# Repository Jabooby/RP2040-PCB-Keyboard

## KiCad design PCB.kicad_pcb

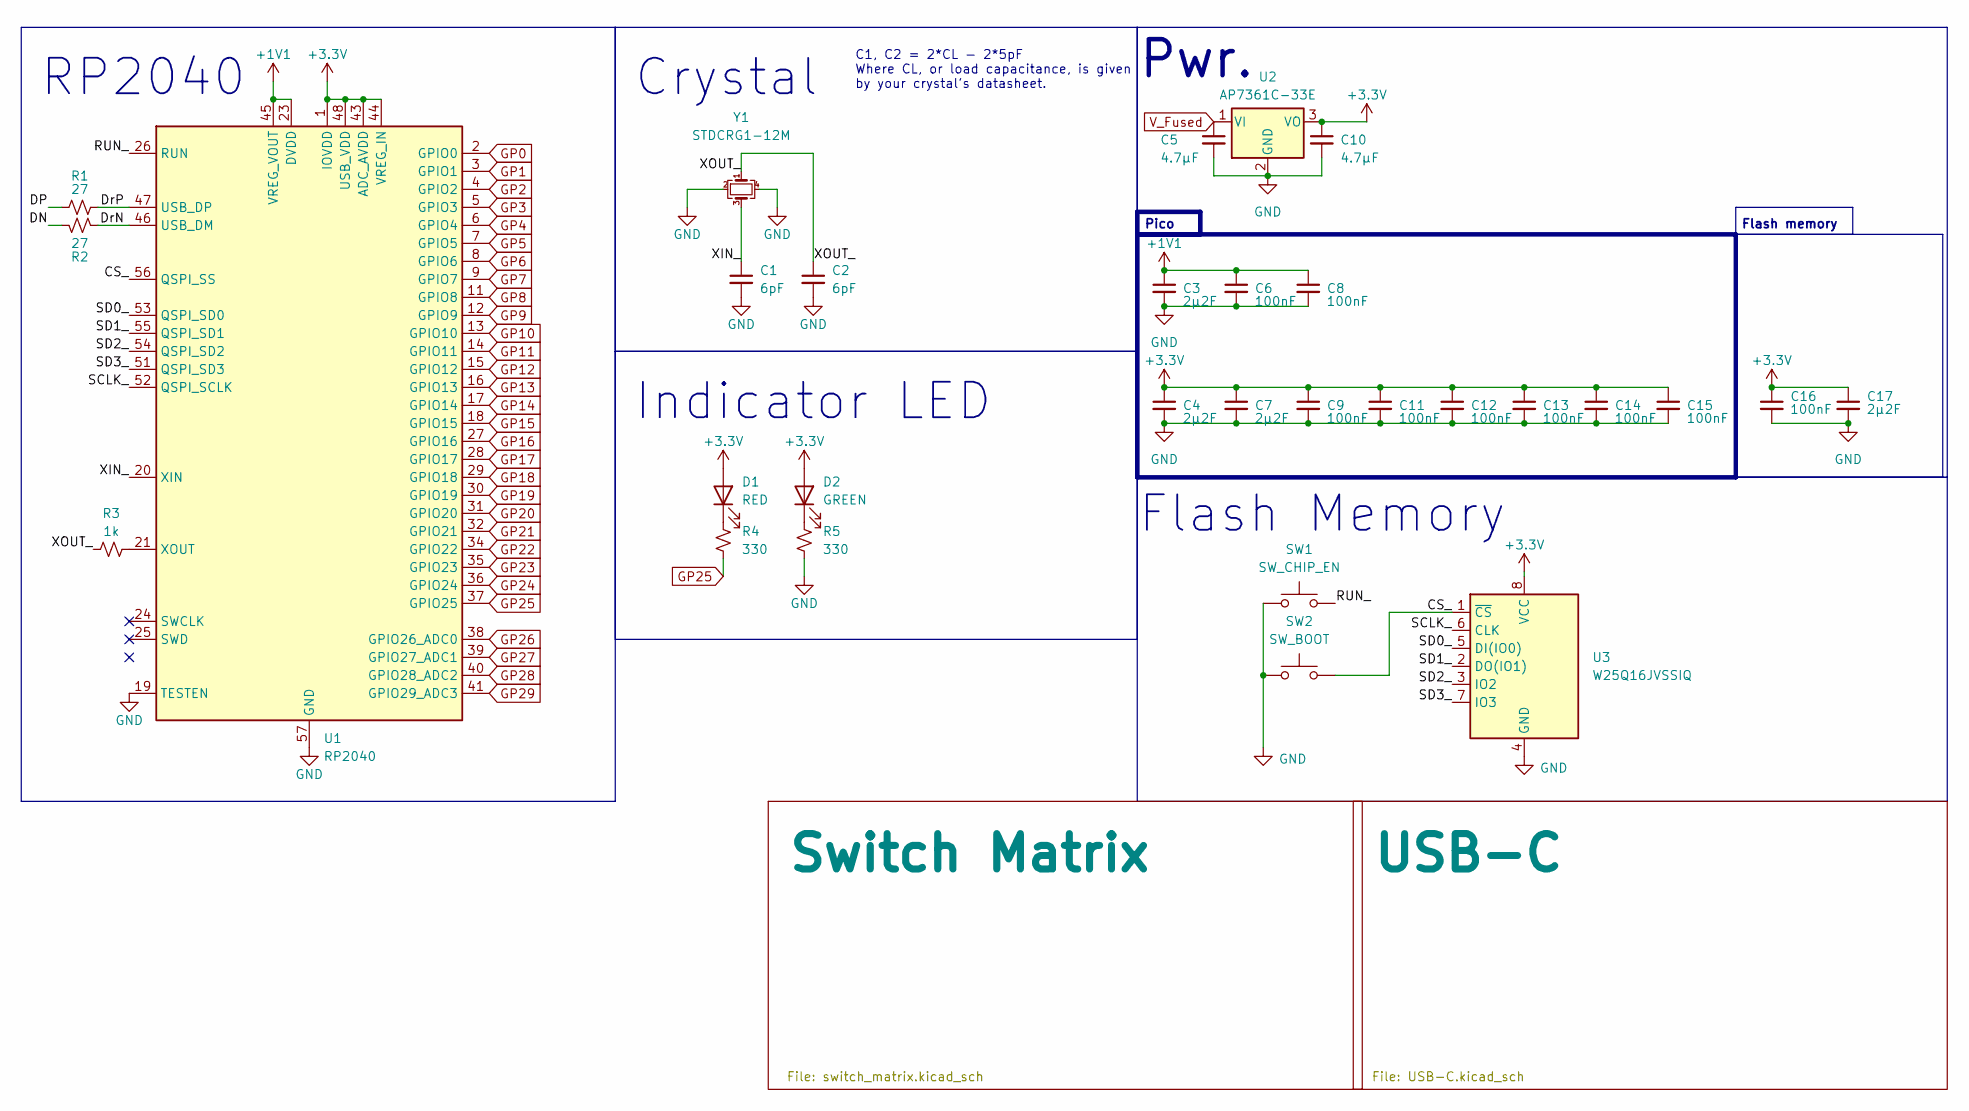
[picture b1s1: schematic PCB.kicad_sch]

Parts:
C1, C2: 6pF; C_0402_1005Metric; LCSC C1562
C3, C4, C17: 2µ2F; C_0805_2012Metric; LCSC C52923
C5, C10: 4.7µF; C_0805_2012Metric; LCSC C52923
C6, C8, C9, C11, C12, C13, C14, C15: 100nF; C_0402_1005Metric; LCSC C1525
C7: 2µ2F; C_0805_2012Metric; LCSC C1525
C16: 100nF; C_0402_1005Metric; LCSC C52923
D1: RED; D_0805_2012Metric
D2: GREEN; D_0805_2012Metric
R1, R2: 27; R_0603_1608Metric; LCSC C25152
R3: 1k; R_0603_1608Metric; LCSC C106235
R4, R5: 330; R_0603_1608Metric
SW1: SW_CHIP_EN; SW_DIP_SPSTx01_Slide_6.7x4.1mm_W6.73mm_P2.54mm_LowProfile_J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
SW2: SW_BOOT; SW_DIP_SPSTx01_Slide_6.7x4.1mm_W6.73mm_P2.54mm_LowProfile_J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
U1: RP2040; QFN-56-1EP_7x7mm_P0.4mm_EP3.2x3.2mm_ThermalVias; LCSC C2040
U2: AP7361C-33E; SOT-223-3_TabPin2
U3: W25Q16JVSSIQ; SOIC-8_5.23x5.23mm_P1.27mm
Y1: STDCRG1-12M; Crystal_SMD_3225-4Pin_3.2x2.5mm; LCSC C9002

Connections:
+1V1: C3.1, C6.1, C8.1, U1.23 (DVDD), U1.45 (VREG_VOUT), U1.50 (DVDD)
+3.3V: C4.1, C7.1, C9.1, C10.1, C11.1, C12.1, C13.1, C14.1, C15.1, C16.1, C17.1, D1.2 (A), D2.2 (A), U1.1 (IOVDD), U1.10 (IOVDD), U1.22 (IOVDD), U1.33 (IOVDD), U1.42 (IOVDD), U1.43 (ADC_AVDD), U1.44 (VREG_IN), U1.48 (USB_VDD), U1.49 (IOVDD), U2.3 (VO), U3.8 (VCC)
/CS_: SW2.2, U1.56 (QSPI_SS), U3.1 (~CS)
/DN: R2.2
/DP: R1.1
/DrN: R2.1, U1.46 (USB_DM)
/DrP: R1.2, U1.47 (USB_DP)
/RUN_: SW1.2, U1.26 (RUN)
/SCLK_: U1.52 (QSPI_SCLK), U3.6 (CLK)
/SD0_: U1.53 (QSPI_SD0), U3.5 (DI(IO0))
/SD1_: U1.55 (QSPI_SD1), U3.2 (DO(IO1))
/SD2_: U1.54 (QSPI_SD2), U3.3 (IO2)
/SD3_: U1.51 (QSPI_SD3), U3.7 (IO3)
/XIN_: C1.1, U1.20 (XIN), Y1.3
/XOUT_: C2.1, R3.1, Y1.1
GND: C1.2, C2.2, C3.2, C4.2, C5.2, C6.2, C7.2, C8.2, C9.2, C10.2, C11.2, C12.2, C13.2, C14.2, C15.2, C16.2, C17.2, R5.2, SW1.1, SW2.1, U1.19 (TESTEN), U1.57 (GND), U2.2 (GND), U3.4 (GND), Y1.2, Y1.4; also elsewhere on the board
GP0: U1.2 (GPIO0); also elsewhere on the board
GP1: U1.3 (GPIO1); also elsewhere on the board
GP2: U1.4 (GPIO2); also elsewhere on the board
GP3: U1.5 (GPIO3); also elsewhere on the board
GP4: U1.6 (GPIO4); also elsewhere on the board
GP5: U1.7 (GPIO5); also elsewhere on the board
GP6: U1.8 (GPIO6); also elsewhere on the board
GP7: U1.9 (GPIO7); also elsewhere on the board
GP8: U1.11 (GPIO8); also elsewhere on the board
GP9: U1.12 (GPIO9); also elsewhere on the board
GP10: U1.13 (GPIO10); also elsewhere on the board
GP11: U1.14 (GPIO11); also elsewhere on the board
GP12: U1.15 (GPIO12); also elsewhere on the board
GP13: U1.16 (GPIO13); also elsewhere on the board
GP14: U1.17 (GPIO14); also elsewhere on the board
GP15: U1.18 (GPIO15); also elsewhere on the board
GP16: U1.27 (GPIO16); also elsewhere on the board
GP17: U1.28 (GPIO17); also elsewhere on the board
GP18: U1.29 (GPIO18); also elsewhere on the board
GP19: U1.30 (GPIO19)
GP20: U1.31 (GPIO20)
GP21: U1.32 (GPIO21)
GP22: U1.34 (GPIO22)
GP23: U1.35 (GPIO23)
GP24: U1.36 (GPIO24)
GP25: R4.2, U1.37 (GPIO25)
GP26: U1.38 (GPIO26_ADC0)
GP27: U1.39 (GPIO27_ADC1)
GP28: U1.40 (GPIO28_ADC2)
GP29: U1.41 (GPIO29_ADC3)
unnamed: D1.1 (K), R4.1
unnamed: D2.1 (K), R5.1
unnamed: R3.2, U1.21 (XOUT)
V_Fused: C5.1, U2.1 (VI); also elsewhere on the board

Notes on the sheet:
Flash memory
Flash Memory
Pwr.
C1, C2 = 2*CL - 2*5pF Where CL, or load capacitance, is given by your crystal's datasheet.
Pico
Indicator LED
Crystal
RP2040

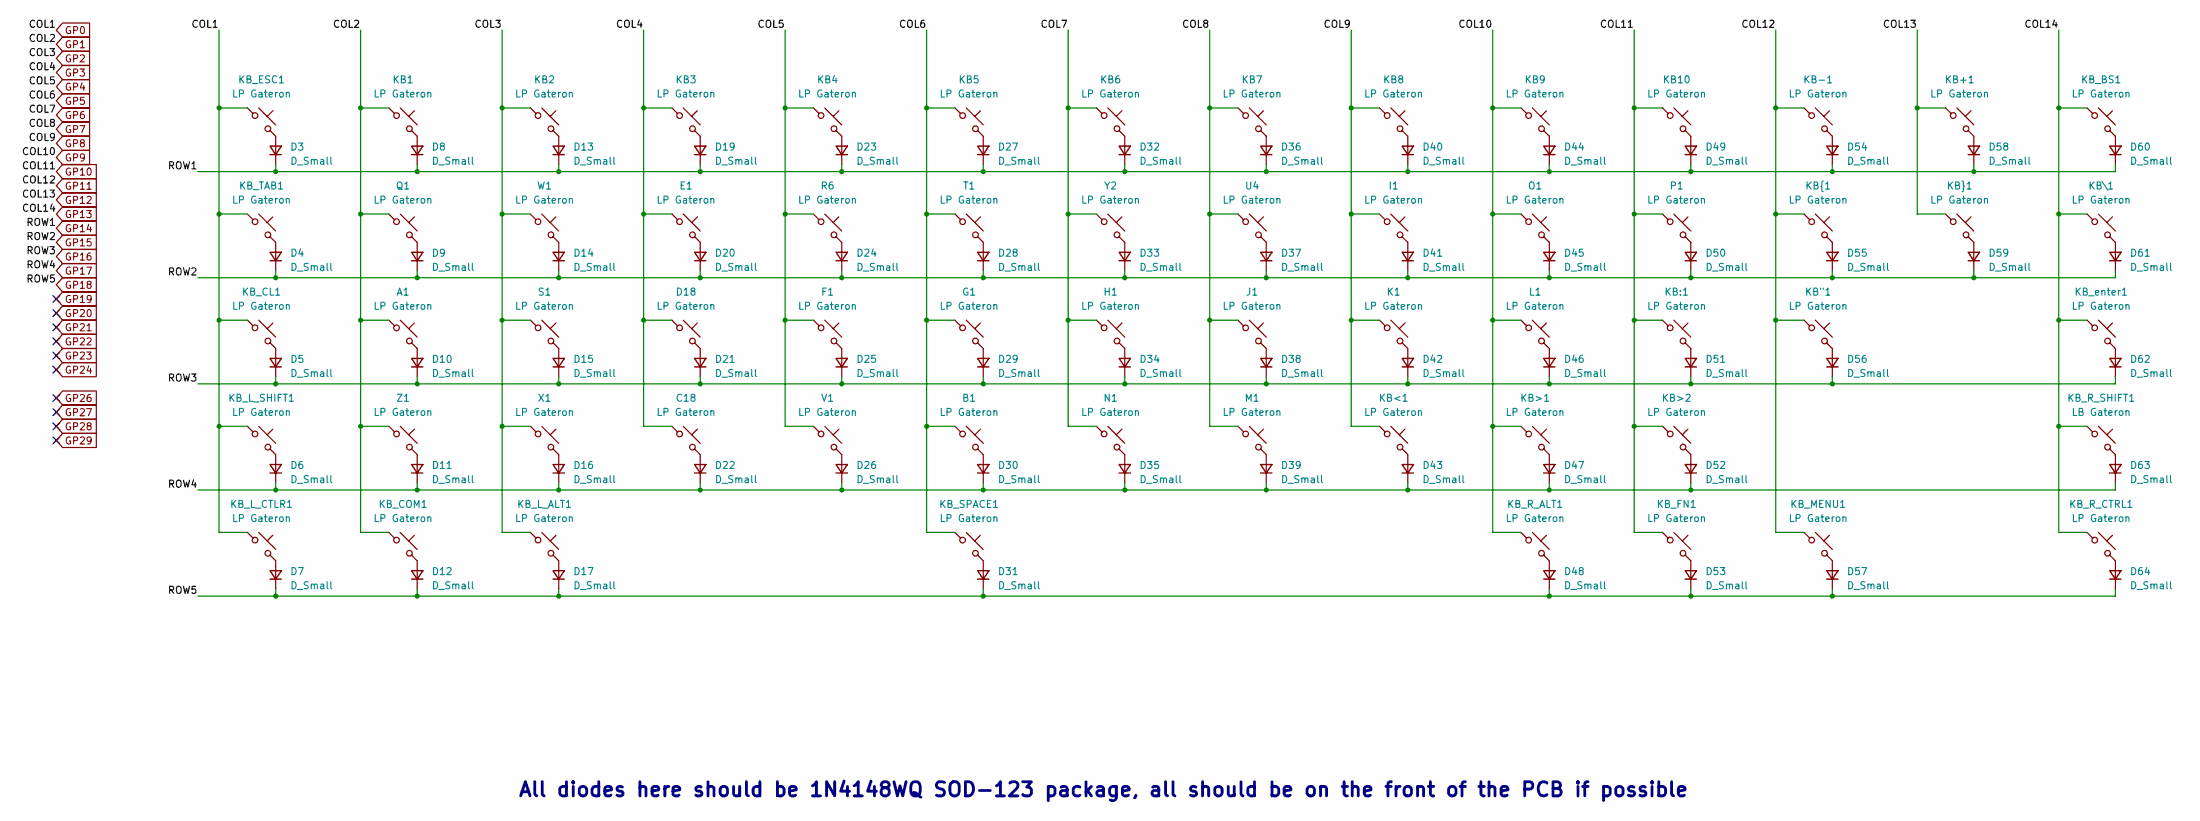
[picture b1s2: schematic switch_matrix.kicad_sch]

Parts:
A1: LP Gateron; SW_Gateron_LowProfile_THT
B1: LP Gateron; SW_Gateron_LowProfile_THT
C18: LP Gateron; SW_Gateron_LowProfile_THT
D3, D4, D5, D6, D7, D8, D9, D10, D11, D12, D13, D14, D15, D16, D17, D19, D20, D21, D22, D23, D24, D25, D26, D27, D28, D29, D30, D31, D32, D33, D34, D35, D36, D37, D38, D39, D40, D41, D42, D43, D44, D45, D46, D47, D48, D49, D50, D51, D52, D53, D54, D55, D56, D57, D58, D59, D60, D61, D62, D63, D64: D_Small; D_SOD-123; LCSC C81598
D18: LP Gateron; SW_Gateron_LowProfile_THT
E1: LP Gateron; SW_Gateron_LowProfile_THT
F1: LP Gateron; SW_Gateron_LowProfile_THT
G1: LP Gateron; SW_Gateron_LowProfile_THT
H1: LP Gateron; SW_Gateron_LowProfile_THT
I1: LP Gateron; SW_Gateron_LowProfile_THT
J1: LP Gateron; SW_Gateron_LowProfile_THT
K1: LP Gateron; SW_Gateron_LowProfile_THT
KB1, KB2, KB3, KB4, KB5, KB6, KB7, KB8, KB9, KB10: LP Gateron; SW_Gateron_LowProfile_THT
KB"1: LP Gateron; SW_Gateron_LowProfile_THT
KB+1: LP Gateron; SW_Gateron_LowProfile_THT
KB-1: LP Gateron; SW_Gateron_LowProfile_THT
KB:1: LP Gateron; SW_Gateron_LowProfile_THT
KB<1: LP Gateron; SW_Gateron_LowProfile_THT
KB>1, KB>2: LP Gateron; SW_Gateron_LowProfile_THT
KB\1: LP Gateron; SW_Gateron_LowProfile_THT
KB_BS1: LP Gateron; SW_Gateron_LowProfile_THT
KB_CL1: LP Gateron; SW_Gateron_LowProfile_THT
KB_COM1: LP Gateron; SW_Gateron_LowProfile_THT
KB_ESC1: LP Gateron; SW_Gateron_LowProfile_THT
KB_FN1: LP Gateron; SW_Gateron_LowProfile_THT
KB_L_ALT1: LP Gateron; SW_Gateron_LowProfile_THT
KB_L_CTLR1: LP Gateron; SW_Gateron_LowProfile_THT
KB_L_SHIFT1: LP Gateron; SW_Gateron_LowProfile_THT
KB_MENU1: LP Gateron; SW_Gateron_LowProfile_THT
KB_R_ALT1: LP Gateron; SW_Gateron_LowProfile_THT
KB_R_CTRL1: LP Gateron; SW_Gateron_LowProfile_THT
KB_R_SHIFT1: LB Gateron; SW_Gateron_LowProfile_THT
KB_SPACE1: LP Gateron; SW_Gateron_LowProfile_THT
KB_TAB1: LP Gateron; SW_Gateron_LowProfile_THT
KB_enter1: LP Gateron; SW_Gateron_LowProfile_THT
KB{1: LP Gateron; SW_Gateron_LowProfile_THT
KB}1: LP Gateron; SW_Gateron_LowProfile_THT
L1: LP Gateron; SW_Gateron_LowProfile_THT
M1: LP Gateron; SW_Gateron_LowProfile_THT
N1: LP Gateron; SW_Gateron_LowProfile_THT
O1: LP Gateron; SW_Gateron_LowProfile_THT
P1: LP Gateron; SW_Gateron_LowProfile_THT
Q1: LP Gateron; SW_Gateron_LowProfile_THT
R6: LP Gateron; SW_Gateron_LowProfile_THT
S1: LP Gateron; SW_Gateron_LowProfile_THT
T1: LP Gateron; SW_Gateron_LowProfile_THT
U4: LP Gateron; SW_Gateron_LowProfile_THT
V1: LP Gateron; SW_Gateron_LowProfile_THT
W1: LP Gateron; SW_Gateron_LowProfile_THT
X1: LP Gateron; SW_Gateron_LowProfile_THT
Y2: LP Gateron; SW_Gateron_LowProfile_THT
Z1: LP Gateron; SW_Gateron_LowProfile_THT

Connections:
GP0: KB_CL1.1, KB_ESC1.1, KB_L_CTLR1.1, KB_L_SHIFT1.1, KB_TAB1.1; also elsewhere on the board
GP1: A1.1, KB1.1, KB_COM1.1, Q1.1, Z1.1; also elsewhere on the board
GP2: KB2.1, KB_L_ALT1.1, S1.1, W1.1, X1.1; also elsewhere on the board
GP3: C18.1, D18.1, E1.1, KB3.1; also elsewhere on the board
GP4: F1.1, KB4.1, R6.1, V1.1; also elsewhere on the board
GP5: B1.1, G1.1, KB5.1, KB_SPACE1.1, T1.1; also elsewhere on the board
GP6: H1.1, KB6.1, N1.1, Y2.1; also elsewhere on the board
GP7: J1.1, KB7.1, M1.1, U4.1; also elsewhere on the board
GP8: I1.1, K1.1, KB8.1, KB<1.1; also elsewhere on the board
GP9: KB9.1, KB>1.1, KB_R_ALT1.1, L1.1, O1.1; also elsewhere on the board
GP10: KB10.1, KB:1.1, KB>2.1, KB_FN1.1, P1.1; also elsewhere on the board
GP11: KB"1.1, KB-1.1, KB_MENU1.1, KB{1.1; also elsewhere on the board
GP12: KB+1.1, KB}1.1; also elsewhere on the board
GP13: KB\1.1, KB_BS1.1, KB_R_CTRL1.1, KB_R_SHIFT1.1, KB_enter1.1; also elsewhere on the board
GP14: D3.1 (K), D8.1 (K), D13.1 (K), D19.1 (K), D23.1 (K), D27.1 (K), D32.1 (K), D36.1 (K), D40.1 (K), D44.1 (K), D49.1 (K), D54.1 (K), D58.1 (K), D60.1 (K); also elsewhere on the board
GP15: D4.1 (K), D9.1 (K), D14.1 (K), D20.1 (K), D24.1 (K), D28.1 (K), D33.1 (K), D37.1 (K), D41.1 (K), D45.1 (K), D50.1 (K), D55.1 (K), D59.1 (K), D61.1 (K); also elsewhere on the board
GP16: D5.1 (K), D10.1 (K), D15.1 (K), D21.1 (K), D25.1 (K), D29.1 (K), D34.1 (K), D38.1 (K), D42.1 (K), D46.1 (K), D51.1 (K), D56.1 (K), D62.1 (K); also elsewhere on the board
GP17: D6.1 (K), D11.1 (K), D16.1 (K), D22.1 (K), D26.1 (K), D30.1 (K), D35.1 (K), D39.1 (K), D43.1 (K), D47.1 (K), D52.1 (K), D63.1 (K); also elsewhere on the board
GP18: D7.1 (K), D12.1 (K), D17.1 (K), D31.1 (K), D48.1 (K), D53.1 (K), D57.1 (K), D64.1 (K); also elsewhere on the board
unnamed: D3.2 (A), KB_ESC1.2
unnamed: D4.2 (A), KB_TAB1.2
unnamed: D5.2 (A), KB_CL1.2
unnamed: D6.2 (A), KB_L_SHIFT1.2
unnamed: D7.2 (A), KB_L_CTLR1.2
unnamed: D8.2 (A), KB1.2
unnamed: D9.2 (A), Q1.2
unnamed: A1.2, D10.2 (A)
unnamed: D11.2 (A), Z1.2
unnamed: D12.2 (A), KB_COM1.2
unnamed: D13.2 (A), KB2.2
unnamed: D14.2 (A), W1.2
unnamed: D15.2 (A), S1.2
unnamed: D16.2 (A), X1.2
unnamed: D17.2 (A), KB_L_ALT1.2
unnamed: D19.2 (A), KB3.2
unnamed: D20.2 (A), E1.2
unnamed: D18.2, D21.2 (A)
unnamed: C18.2, D22.2 (A)
unnamed: D23.2 (A), KB4.2
unnamed: D24.2 (A), R6.2
unnamed: D25.2 (A), F1.2
unnamed: D26.2 (A), V1.2
unnamed: D27.2 (A), KB5.2
unnamed: D28.2 (A), T1.2
unnamed: D29.2 (A), G1.2
unnamed: B1.2, D30.2 (A)
unnamed: D31.2 (A), KB_SPACE1.2
unnamed: D32.2 (A), KB6.2
unnamed: D33.2 (A), Y2.2
unnamed: D34.2 (A), H1.2
unnamed: D35.2 (A), N1.2
unnamed: D36.2 (A), KB7.2
unnamed: D37.2 (A), U4.2
unnamed: D38.2 (A), J1.2
unnamed: D39.2 (A), M1.2
unnamed: D40.2 (A), KB8.2
unnamed: D41.2 (A), I1.2
unnamed: D42.2 (A), K1.2
unnamed: D43.2 (A), KB<1.2
unnamed: D44.2 (A), KB9.2
unnamed: D45.2 (A), O1.2
unnamed: D46.2 (A), L1.2
unnamed: D47.2 (A), KB>1.2
unnamed: D48.2 (A), KB_R_ALT1.2
unnamed: D49.2 (A), KB10.2
unnamed: D50.2 (A), P1.2
unnamed: D51.2 (A), KB:1.2
unnamed: D52.2 (A), KB>2.2
unnamed: D53.2 (A), KB_FN1.2
unnamed: D54.2 (A), KB-1.2
unnamed: D55.2 (A), KB{1.2
unnamed: D56.2 (A), KB"1.2
unnamed: D57.2 (A), KB_MENU1.2
unnamed: D58.2 (A), KB+1.2
unnamed: D59.2 (A), KB}1.2
unnamed: D60.2 (A), KB_BS1.2
unnamed: D61.2 (A), KB\1.2
unnamed: D62.2 (A), KB_enter1.2
unnamed: D63.2 (A), KB_R_SHIFT1.2
unnamed: D64.2 (A), KB_R_CTRL1.2

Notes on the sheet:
All diodes here should be 1N4148WQ SOD-123 package, all should be on the front of the PCB if possible

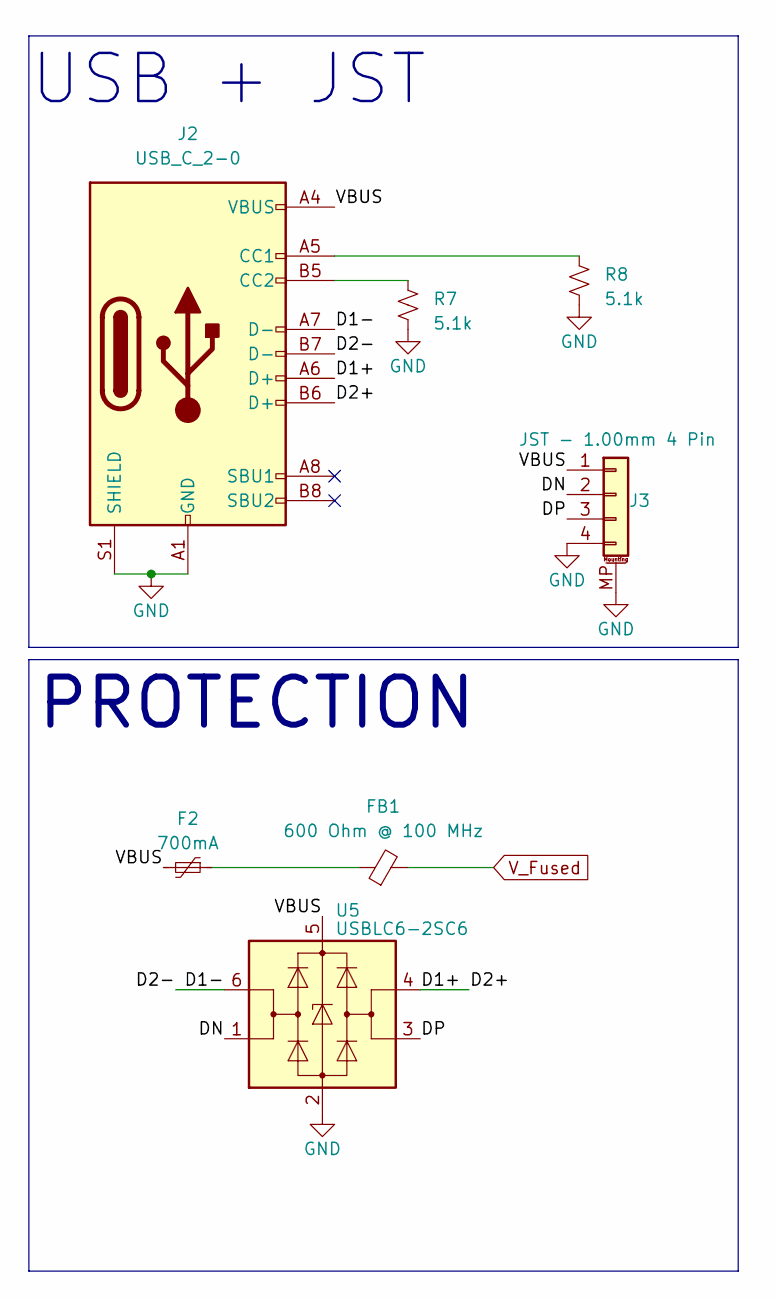
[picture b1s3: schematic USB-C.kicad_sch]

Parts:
F2: 700mA; Fuse_0805_2012Metric; LCSC C914086
FB1: 600 Ohm @ 100 MHz; L_0805_2012Metric; LCSC C85812
J2: USB_C_2-0; USB_C_Receptacle_G-Switch_GT-USB-7010ASV
J3: JST - 1.00mm 4 Pin; JST_SH_SM04B-SRSS-TB_1x04-1MP_P1.00mm_Horizontal; LCSC C160404
R7, R8: 5.1k; R_0603_1608Metric; LCSC C25905
U5: USBLC6-2SC6; SOT-23-6; LCSC C558442

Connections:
/USB-C/D1+: J2.A6 (D+), J2.B6 (D+), U5.4 (I/O2)
/USB-C/D1-: J2.A7 (D-), J2.B7 (D-), U5.6 (I/O1)
/USB-C/DN: J3.2, U5.1 (I/O1)
/USB-C/DP: J3.3, U5.3 (I/O2)
/USB-C/VBUS: F2.2, J2.A4 (VBUS), J2.A9 (VBUS), J2.B4 (VBUS), J2.B9 (VBUS), J3.1, U5.5 (VBUS)
GND: J2.A1 (GND), J2.A12 (GND), J2.B1 (GND), J2.B12 (GND), J2.S1 (SHIELD), J3.4, J3.MP (MountPin), R7.1, R8.1, U5.2 (GND); also elsewhere on the board
unnamed: F2.1, FB1.1
unnamed: J2.A5 (CC1), R8.2
unnamed: J2.B5 (CC2), R7.2
V_Fused: FB1.2; also elsewhere on the board

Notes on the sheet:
USB + JST
PROTECTION

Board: 4 copper layers, 162 parts (96 on the bottom side), 107 nets, no tracks yet.

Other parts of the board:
H3, H5: MountingHole; PKRHSL
H4: MountingHole; PKRH

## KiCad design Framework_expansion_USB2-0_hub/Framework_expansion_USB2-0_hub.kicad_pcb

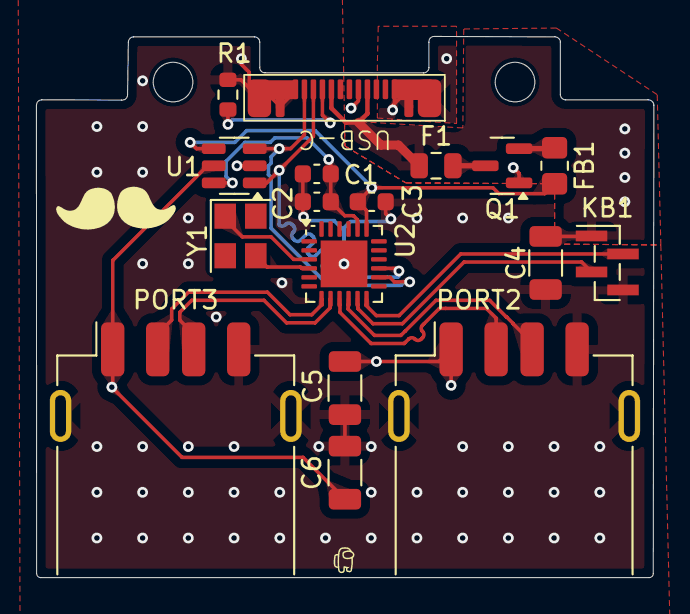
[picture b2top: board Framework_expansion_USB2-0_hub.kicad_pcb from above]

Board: 2 copper layers, 34.3 x 30.1 mm, 19 parts (0 on the bottom side), 17 nets.

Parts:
C1, C3: 10µF; C_0603_1608Metric
C2: 1µF; C_0603_1608Metric
C4, C5, C6: 100µF; C_1206_3216Metric
F1: SMD0805B110TF; Fuse_0805_2012Metric
FB1: 600 @ 100MHz; R_0805_2012Metric_Pad1.20x1.40mm_HandSolder
H1, H2: MountingHole; MountingHole_2.2mm_M2
KB1: Keyboard pin header; PinHeader_1x04_P1.00mm_Vertical_SMD_Pin1Left
PORT2, PORT3: USB_A; USB_A_Receptacle_GCT_USB1046
Q1: AO3401A; SOT-23
R1: 5.1k; R_0603_1608Metric
U1: SRV05-4; SOT-23-6
U2: HVQFN-24-1EP_4x4mm_P0.5mm_EP2.6x2.6mm
USB-C: USB_C_Plug_USB2.0; UP20-C-F-G-FL-1-P12-TR
Y1: 12MHz; Crystal_SMD_3225-4Pin_3.2x2.5mm

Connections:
+3V3: C1.1, C2.1, U1.6 (IO4), U2.20 (+3V3)
+5V: C3.1, FB1.2, U1.4 (IO3), U2.19 (+V5)
/D2+: PORT2.3 (D+), U2.10 (D_{+2})
/D2-: PORT2.2 (D-), U2.9 (D_{-2})
/D3+: PORT3.3 (D+), U2.8 (D_{+3})
/D3-: PORT3.2 (D-), U2.7 (D_{-3})
/D+: U1.1 (IO1), U2.15 (D_{+U}), USB-C.A6 (D+)
/D-: U1.3 (IO2), U2.14 (D_{-U}), USB-C.A7 (D-)
/KB+: KB1.2, U2.12 (D_{+1})
/KB-: KB1.3, U2.11 (D_{-1})
GND: C1.2, C2.2, C3.2, C4.2, C5.2, C6.2, KB1.4, PORT2.4 (GND), PORT2.5 (Shield), PORT3.4 (GND), PORT3.5 (Shield), Q1.1 (G), R1.2, U1.2 (VN), U2.25 (GND), USB-C.25 (SHIELD), USB-C.26 (SHIELD), USB-C.A1 (GND), USB-C.A12 (GND), USB-C.B12 (GND)
unnamed: R1.1, USB-C.A5 (CC)
unnamed: F1.2, Q1.3 (D)
unnamed: FB1.1, Q1.2 (S)
unnamed: U2.4 (X_{IN}), Y1.2
unnamed: U2.3 (X_{OUT}), Y1.1
VBUS: C4.1, C5.1, C6.1, F1.1, KB1.1, PORT2.1 (VBUS), PORT3.1 (VBUS), U1.5 (VP), USB-C.A4 (VBUS), USB-C.B9 (VBUS)

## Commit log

2024-10-29 push curstom hub USB2.0
2024-10-30 update to kicad 8
2024-10-31 keyboard switch comletion
2024-11-01 push de modification
2025-03-10 push schema électrique
2025-04-30 push pas sûr quoi exactement
